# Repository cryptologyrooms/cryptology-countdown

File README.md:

# cryptology-countdown
PCBs and software for two synchronous countdown timers

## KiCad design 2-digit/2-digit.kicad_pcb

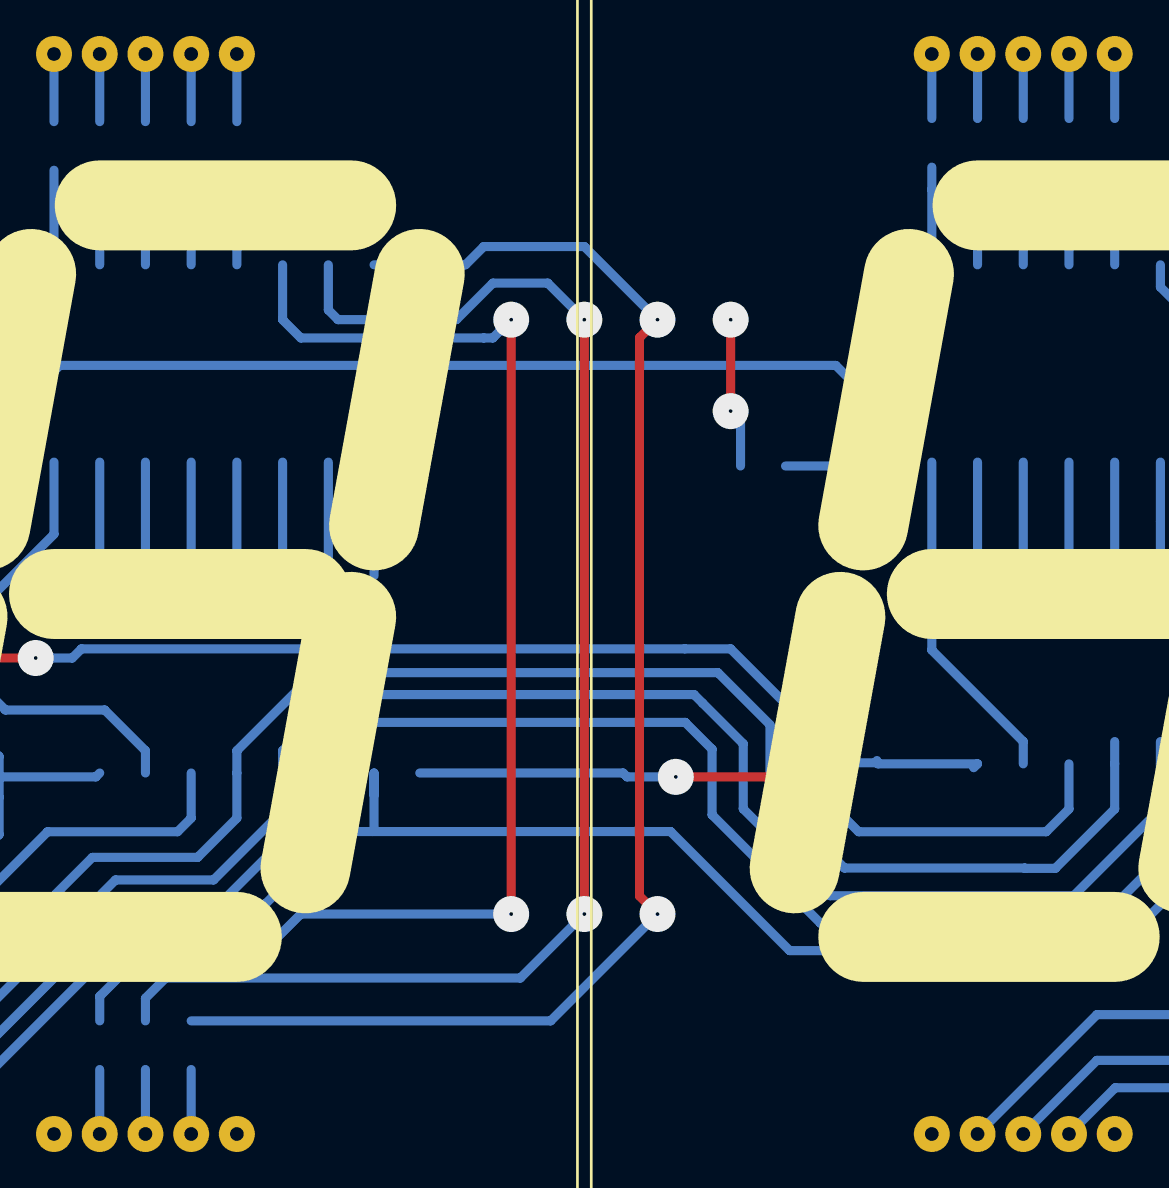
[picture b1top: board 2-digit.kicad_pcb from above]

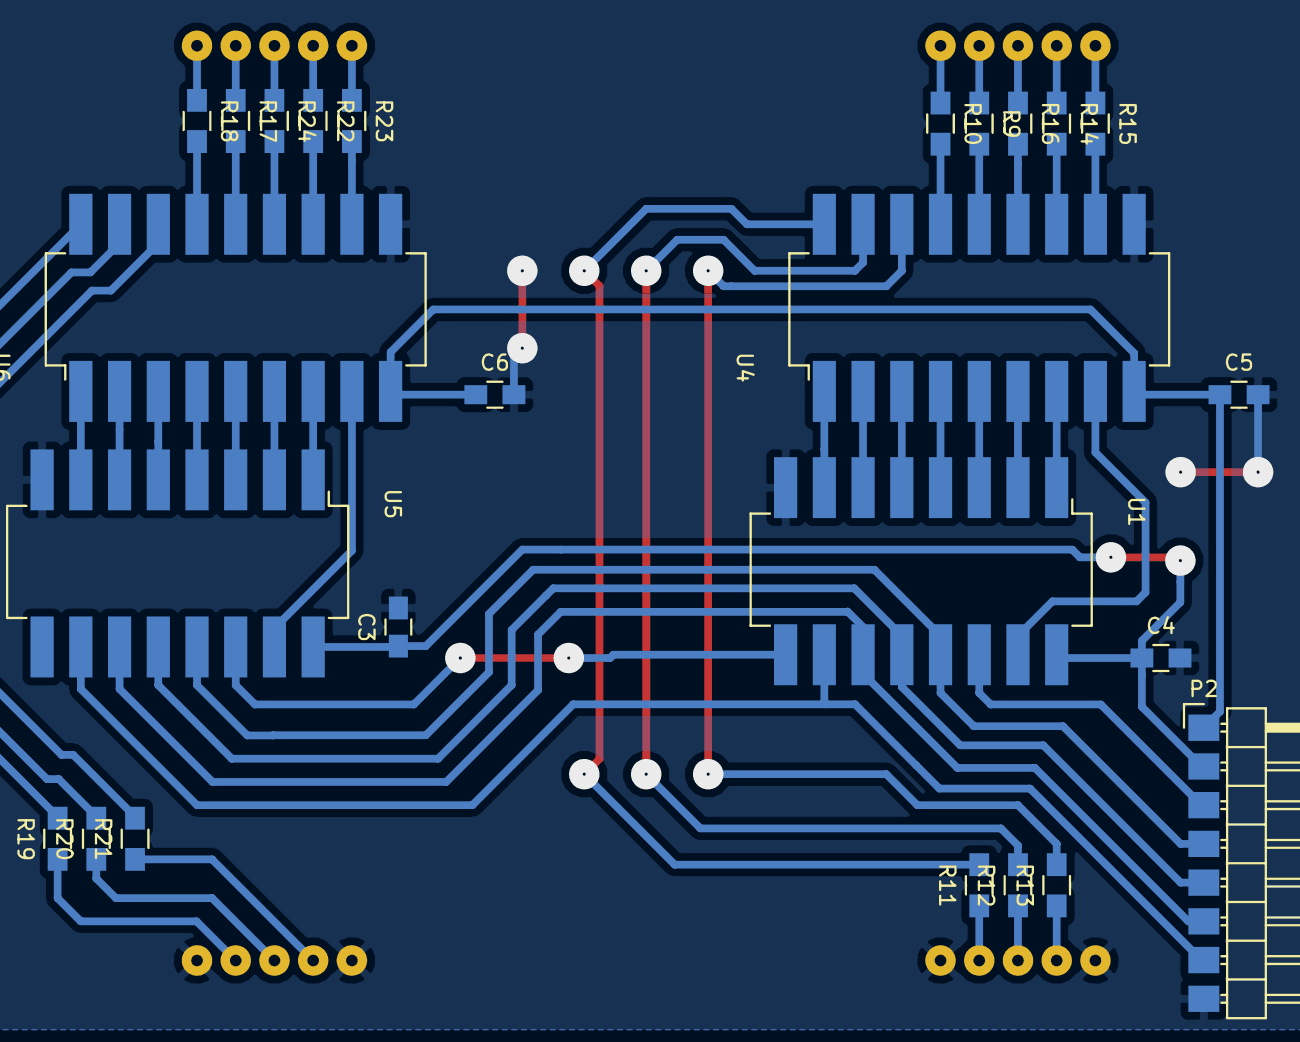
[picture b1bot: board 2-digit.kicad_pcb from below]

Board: 2 copper layers, 27 parts (25 on the bottom side), 57 nets.

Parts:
C3, C4, C5, C6: C; C_0805_HandSoldering
P2: CONN_01X08; SIP8-SMT
R9, R10, R11, R12, R13, R14, R15, R16, R17, R18, R19, R20, R21, R22, R23, R24: R; R_0805_HandSoldering
U1, U5: 74HC595; DIP16-SMT
U4, U6: UDN2981; DIP18-SMT
U8, U9: FJS23101AH

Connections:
+5V: C3.1, C4.1, P2.2, U1.16, U5.16
+9V: C5.1, C6.1, P2.1, U4.9, U6.9
/CLK: P2.6, U1.11, U5.11
/DATA_IN: P2.3, U1.14
/LATCH: P2.5, U1.12, U5.12
/SEG1A: R9.2, U4.14
/SEG1B: R10.2, U4.15
/SEG1C: R11.2, U4.18
/SEG1D: R12.2, U4.17
/SEG1DP: R16.2, U4.13
/SEG1E: R13.2, U4.16
/SEG1F: R14.2, U4.12
/SEG1G: R15.2, U4.11
/SEG2A: R17.2, U6.14
/SEG2B: R18.2, U6.15
/SEG2C: R19.2, U6.18
/SEG2D: R20.2, U6.17
/SEG2DP: R24.2, U6.13
/SEG2E: R21.2, U6.16
/SEG2F: R22.2, U6.12
/SEG2G: R23.2, U6.11
/SIG1A: U1.3, U4.5
/SIG1B: U1.4, U4.4
/SIG1C: U1.7, U4.1
/SIG1D: U1.6, U4.2
/SIG1DP: U1.2, U4.6
/SIG1E: U1.5, U4.3
/SIG1F: U1.1, U4.7
/SIG1G: U1.15, U4.8
/SIG2A: U5.3, U6.5
/SIG2B: U5.4, U6.4
/SIG2C: U5.7, U6.1
/SIG2D: U5.6, U6.2
/SIG2DP: U5.2, U6.6
/SIG2E: U5.5, U6.3
/SIG2F: U5.1, U6.7
/SIG2G: U5.15, U6.8
/~CLR: P2.7, U1.10, U5.10
/~OE: P2.4, U1.13, U5.13
GND: C3.2, C4.2, C5.2, C6.2, P2.8, U1.8, U4.10, U5.8, U6.10, U8.6, U8.10, U9.6, U9.10
unnamed: R9.1, U8.4
unnamed: R10.1, U8.5
unnamed: R11.1, U8.7
unnamed: R12.1, U8.8
unnamed: R13.1, U8.9
unnamed: R14.1, U8.2
unnamed: R15.1, U8.1
unnamed: R16.1, U8.3
unnamed: R17.1, U9.4
unnamed: R18.1, U9.5
unnamed: R19.1, U9.7
unnamed: R20.1, U9.8
unnamed: R21.1, U9.9
unnamed: R22.1, U9.2
unnamed: R23.1, U9.1
unnamed: R24.1, U9.3
unnamed: U1.9, U5.14

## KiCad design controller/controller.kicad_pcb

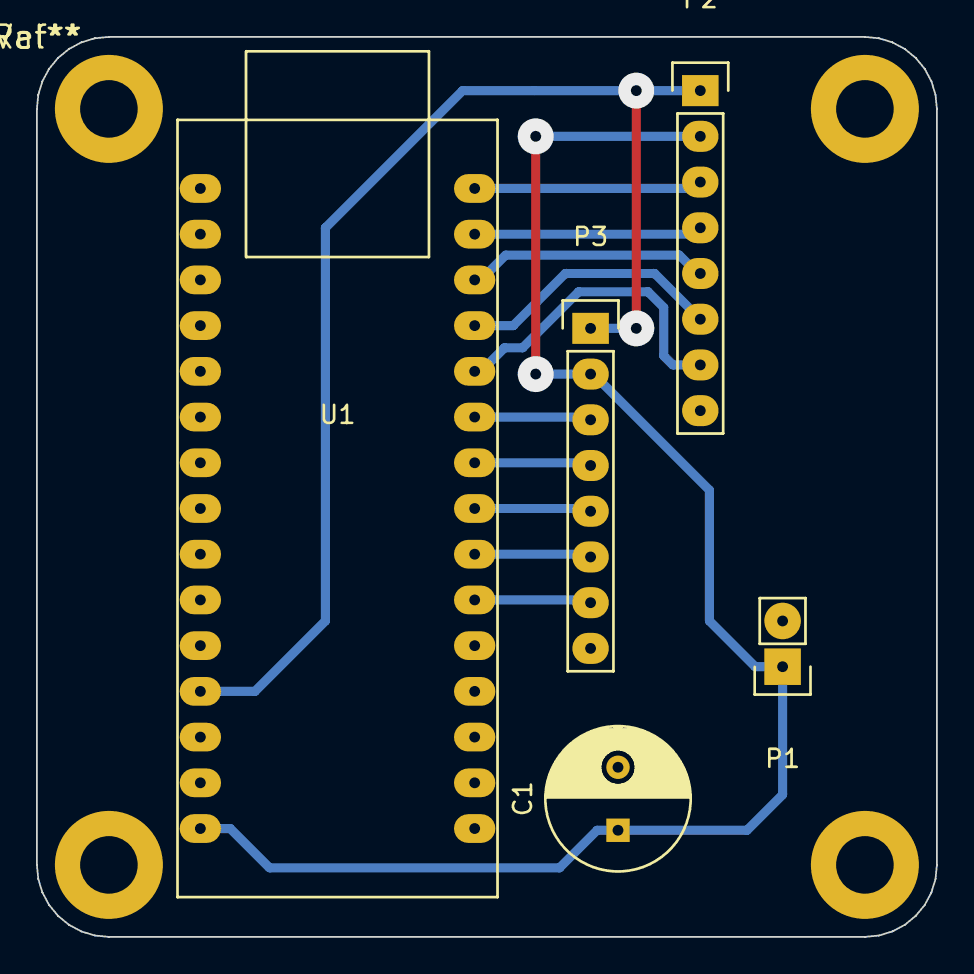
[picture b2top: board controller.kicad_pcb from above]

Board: 2 copper layers, 50.0 x 50.0 mm, 6 parts (0 on the bottom side), 13 nets.

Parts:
C1: C; C_Radial_D8_L11.5_P3.5
P1: CONN_01X02; Pin_Header_Straight_1x02
P2, P3: CONN_01X08; Pin_Header_Straight_1x08
Ref**: Val**; DP5050
U1: arduino_nano; nano-longpads

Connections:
+5V: P2.1, P3.1, U1.12
+9V: C1.1, P1.1, P2.2, P3.2, U1.15
GND: C1.2, P1.2, P2.8, P3.8, U1.14, U1.19
unnamed: P2.3, U1.30
unnamed: P2.4, U1.29
unnamed: P2.5, U1.28
unnamed: P2.6, U1.27
unnamed: P2.7, U1.26
unnamed: P3.3, U1.25
unnamed: P3.4, U1.24
unnamed: P3.5, U1.23
unnamed: P3.6, U1.22
unnamed: P3.7, U1.21

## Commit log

2016-07-10 First complete software revision
2016-07-10 Updated .gitignore
2016-07-10 Add 2-digit display
2016-07-11 Latest 2-digit PCB
2016-07-11 Fixed 2-digit display code
2016-07-11 Added draft casing design
